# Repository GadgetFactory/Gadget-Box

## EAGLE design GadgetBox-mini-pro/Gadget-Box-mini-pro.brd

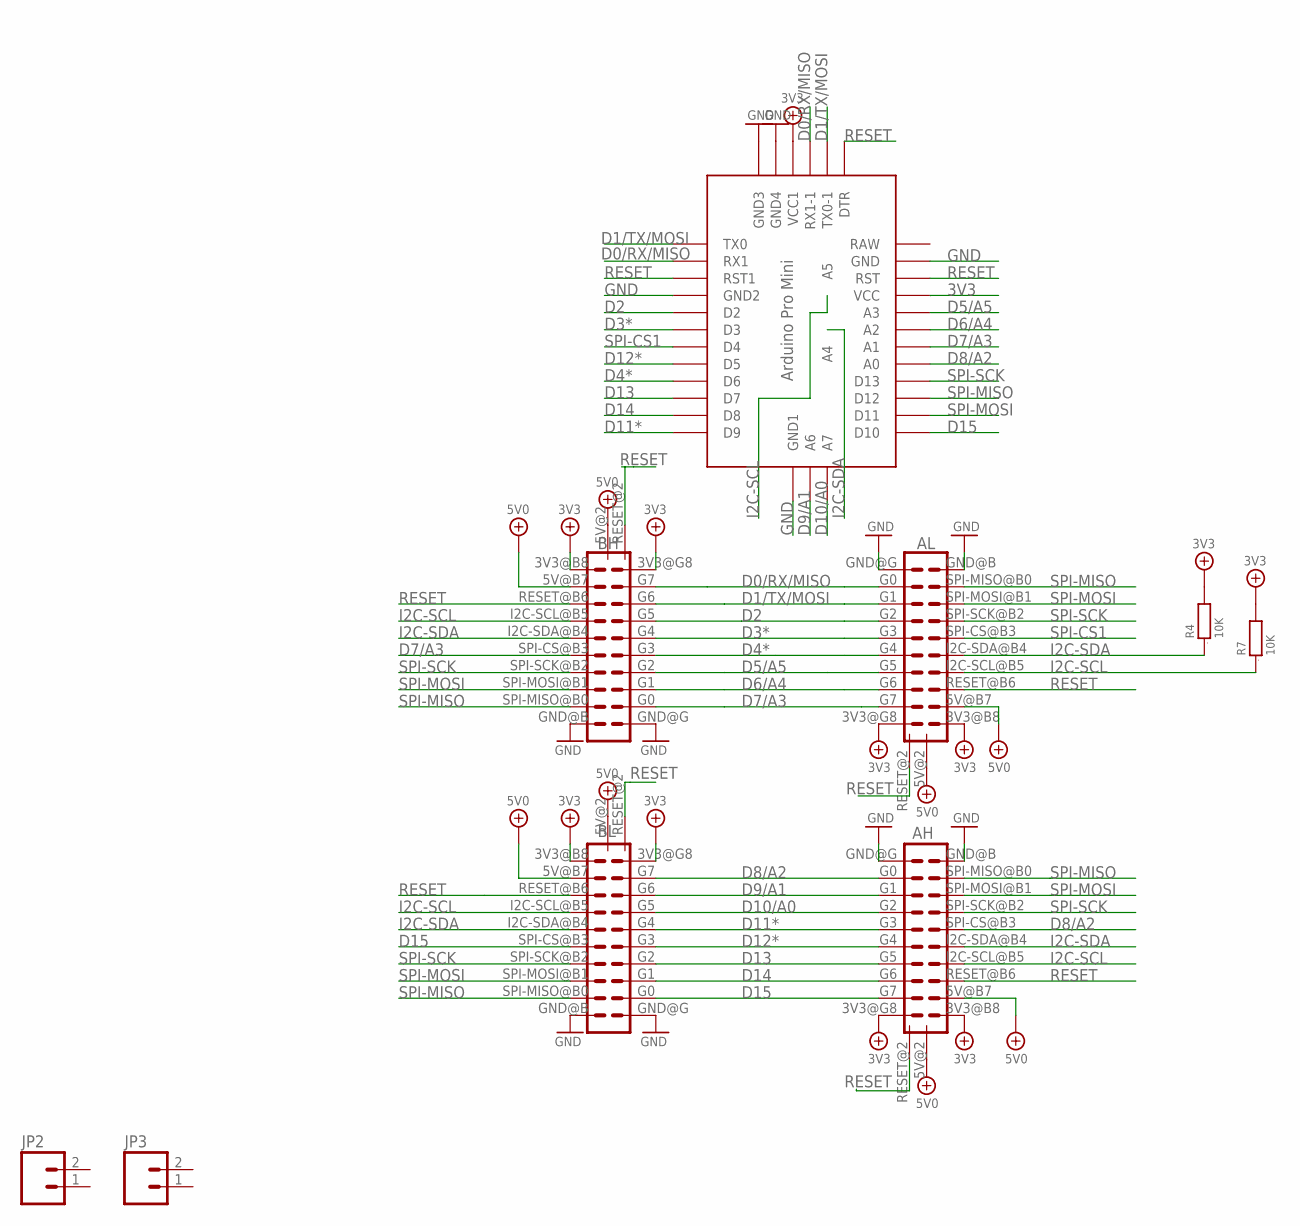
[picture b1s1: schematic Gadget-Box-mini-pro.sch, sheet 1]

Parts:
AH: ECOGECOG_SLOT_ALT1; ECOG_ALT1; PARTNO PPPC102LFBN-RC,SULLINS CONNECTOR SOLUTI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
AL: ECOGECOG_SLOT_ALT1; ECOG_ALT1; PARTNO PPPC102LFBN-RC,SULLINS CONNECTOR SOLUTI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
BH: ECOGECOG_SLOT_ALT1; ECOG_ALT1; PARTNO PPPC102LFBN-RC,SULLINS CONNECTOR SOLUTI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
BL: ECOGECOG_SLOT_ALT1; ECOG_ALT1; PARTNO PPPC102LFBN-RC,SULLINS CONNECTOR SOLUTI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
JP2, JP3: M021X02_NO_SILK; 1X02_NO_SILK; PARTNO PPPC021LFBN-RC,SULLINS CONNECTOR SOLUTI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
R4, R7: 10K; 0603; PARTNO RC0603JR-0710KL,YAGEO (VA),dk,311-10KGR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
U$1: ABK-PRO-MINI

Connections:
3V3: AH.3V3@B8 (3V3), AH.3V3@G8 (3V3), AL.3V3@B8 (3V3), AL.3V3@G8 (3V3), BH.3V3@B8 (3V3), BH.3V3@G8 (3V3), BL.3V3@B8 (3V3), BL.3V3@G8 (3V3), R4.2, R7.2, U$1.VCC, U$1.VCC1; also elsewhere on the board
5V0: AH.5V@2 (5V), AH.5V@B7 (5V), AL.5V@2 (5V), AL.5V@B7 (5V), BH.5V@2 (5V), BH.5V@B7 (5V), BL.5V@2 (5V), BL.5V@B7 (5V); also elsewhere on the board
D0/RX/MISO: AL.G0, BH.G7, U$1.RX1, U$1.RX1-1
D1/TX/MOSI: AL.G1, BH.G6, U$1.TX0, U$1.TX0-1
D2: AL.G2, BH.G5, U$1.D2
D3*: AL.G3, BH.G4, U$1.D3
D4*: AL.G4, BH.G3, U$1.D6
D5/A5: AL.G5, BH.G2, U$1.A3; also elsewhere on the board
D6/A4: AL.G6, BH.G1, U$1.A2
D7/A3: AL.G7, BH.G0, BH.SPI-CS@B3 (SPI-CS), U$1.A1
D8/A2: AH.G0, AH.SPI-CS@B3 (SPI-CS), BL.G7, U$1.A0
D9/A1: AH.G1, BL.G6, U$1.A6
D10/A0: AH.G2, BL.G5, U$1.A7
D11*: AH.G3, BL.G4, U$1.D9
D12*: AH.G4, BL.G3, U$1.D5
D13: AH.G5, BL.G2, U$1.D7
D14: AH.G6, BL.G1, U$1.D8
D15: AH.G7, BL.G0, BL.SPI-CS@B3 (SPI-CS), U$1.D10
GND: AH.GND@B (GND), AH.GND@G (GND), AL.GND@B (GND), AL.GND@G (GND), BH.GND@B (GND), BH.GND@G (GND), BL.GND@B (GND), BL.GND@G (GND), U$1.GND, U$1.GND1 (GND2), U$1.GND2 (GND3), U$1.GND3 (GND4), U$1.GND4 (GND1); also elsewhere on the board
I2C-SCL: AH.I2C-SCL@B5 (I2C-SCL), AL.I2C-SCL@B5 (I2C-SCL), BH.I2C-SCL@B5 (I2C-SCL), BL.I2C-SCL@B5 (I2C-SCL), R7.1, U$1.A5
I2C-SDA: AH.I2C-SDA@B4 (I2C-SDA), AL.I2C-SDA@B4 (I2C-SDA), BH.I2C-SDA@B4 (I2C-SDA), BL.I2C-SDA@B4 (I2C-SDA), R4.1, U$1.A4
RESET: AH.RESET@2 (RESET), AH.RESET@B6 (RESET), AL.RESET@2 (RESET), AL.RESET@B6 (RESET), BH.RESET@2 (RESET), BH.RESET@B6 (RESET), BL.RESET@2 (RESET), BL.RESET@B6 (RESET), U$1.DTR, U$1.RST, U$1.RST1
SPI-CS1: AL.SPI-CS@B3 (SPI-CS), U$1.D4
SPI-MISO: AH.SPI-MISO@B0 (SPI-MISO), AL.SPI-MISO@B0 (SPI-MISO), BH.SPI-MISO@B0 (SPI-MISO), BL.SPI-MISO@B0 (SPI-MISO), U$1.D12
SPI-MOSI: AH.SPI-MOSI@B1 (SPI-MOSI), AL.SPI-MOSI@B1 (SPI-MOSI), BH.SPI-MOSI@B1 (SPI-MOSI), BL.SPI-MOSI@B1 (SPI-MOSI), U$1.D11
SPI-SCK: AH.SPI-SCK@B2 (SPI-SCK), AL.SPI-SCK@B2 (SPI-SCK), BH.SPI-SCK@B2 (SPI-SCK), BL.SPI-SCK@B2 (SPI-SCK), U$1.D13

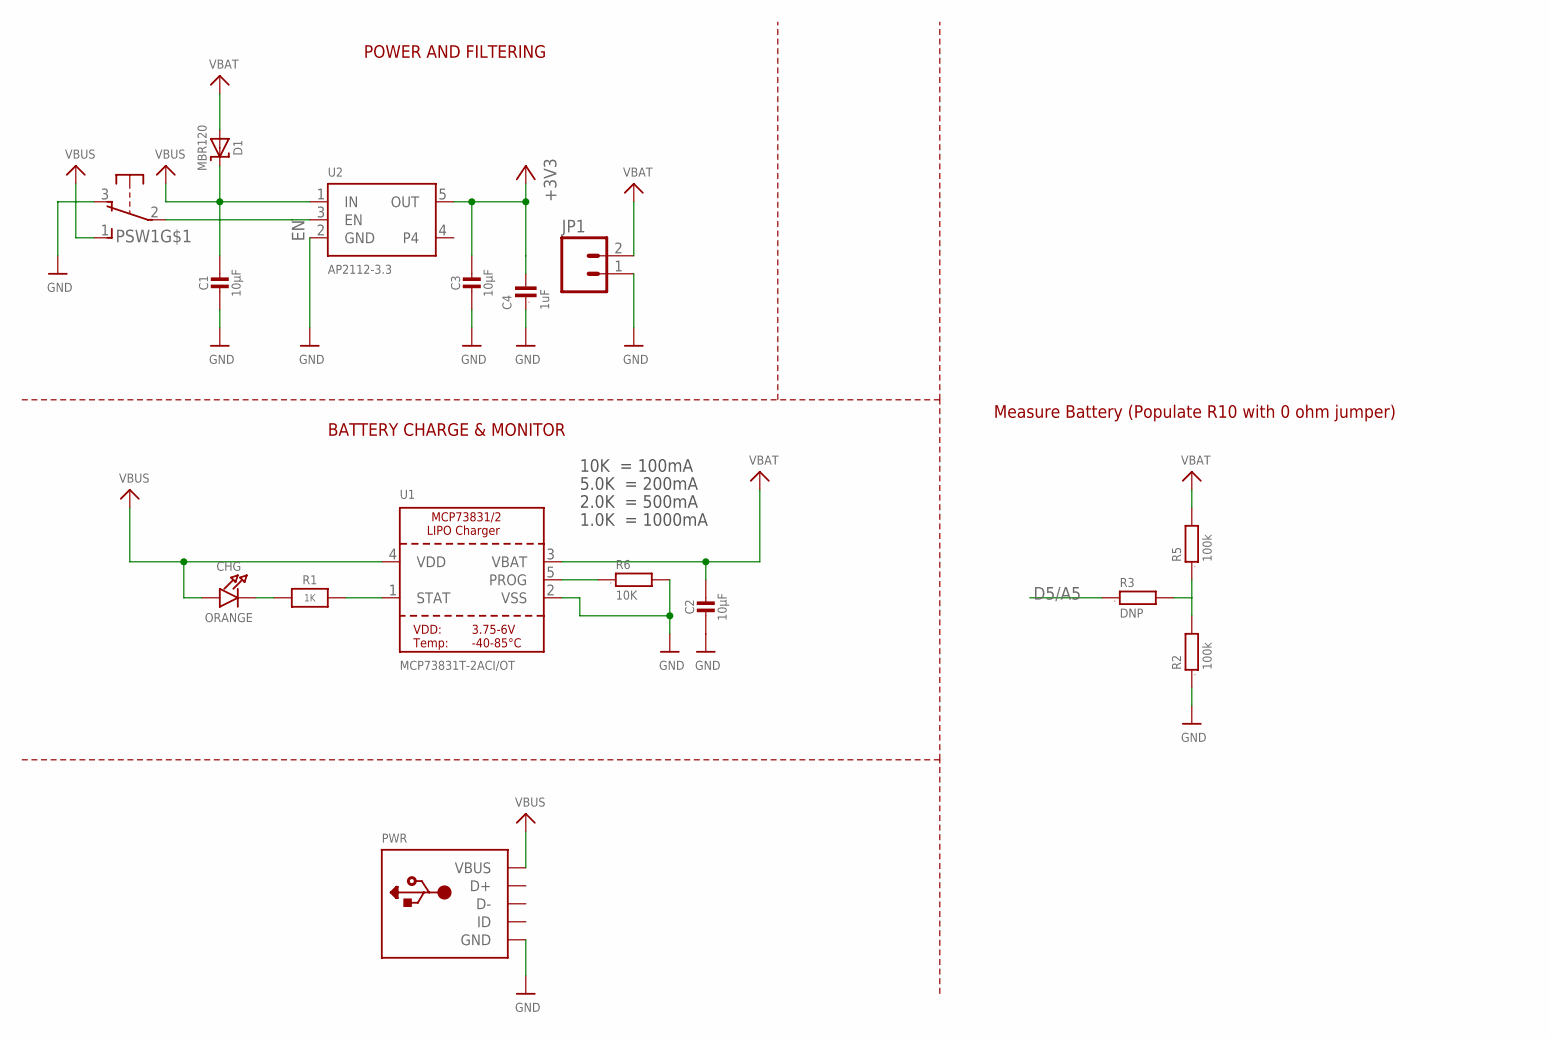
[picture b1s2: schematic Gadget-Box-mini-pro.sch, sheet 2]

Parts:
C1, C2, C3: 10µF; 0805-NO; PARTNO CL21F106ZPFNNNE,Samsung,DK,1276-3012-1-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
C4: 1uF; 0603; PARTNO C1608X5R1A105K080AC,TDK CORPORATION (VA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
CHG: ORANGE; CHIPLED_0805_NOOUTLINE; PARTNO LTST-C171EKT,LITE-ON INC (VA),DK,160-14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
D1: MBR120; SOD-123; PARTNO MBR120VLSFT3G,on semiconductor,dk,MBR12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
JP1: M02-JST-2-PTH-NO_SILK; JST-2-PTH-NS; PARTNO B2B-PH-SM4-TB(LF)(SN),JST SALES AMERICA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
PSW1: OS102011MA1Q; PARTNO OS102011MA1QN1,C&K Components,dk,CKN955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
PWR: USBMINIB; USB-MINIB; PARTNO USB-M26FTR,On Shore Technology Inc,DK,E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
R1: 1K; 0603-NO; PARTNO RC0603JR-071KL,YAGEO (VA),dk,311-1.0KGR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
R2, R5: 100k; 0603; PARTNO RC0603JR-07100KL,YAGEO (VA),dk,311-100K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
R3: DNP; 0603
R6: 10K; 0603; PARTNO RC0603JR-0710KL,YAGEO (VA),dk,311-10KGR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
U1: MCP73831T-2ACI/OT; SOT23-5; PARTNO MCP73831T-2ACI/OT,MICROCHIP TECHNOLOGY 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
U2: AP2112-3.3; SOT23-5; PARTNO AP2112K-3.3TRG1,Diodes Incorporated,dk,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

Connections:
3V3: C3.1, C4.2, U2.5 (OUT); also elsewhere on the board
5V0: C1.1, CHG.A, D1.C, PSW1.1 (S), PWR.VBUS, U1.4 (VDD), U2.1 (IN); also elsewhere on the board
D5/A5: R3.1; also elsewhere on the board
EN: PSW1.2, U2.3 (EN)
GND: C1.2, C2.2, C3.2, C4.1, JP1.1, PSW1.3 (O), PWR.GND, R2.1, R6.2, U1.2 (VSS), U2.2 (GND); also elsewhere on the board
unnamed: CHG.C, R1.1
unnamed: R2.2, R3.2, R5.1
unnamed: R1.2, U1.1 (STAT)
unnamed: R6.1, U1.5 (PROG)
VBAT: C2.1, D1.A, JP1.2, R5.2, U1.3 (VBAT)

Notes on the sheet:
POWER AND FILTERING
10K = 100mA
5.0K = 200mA
2.0K = 500mA
1.0K = 1000mA
BATTERY CHARGE & MONITOR
Measure Battery (Populate R10 with 0 ohm jumper)

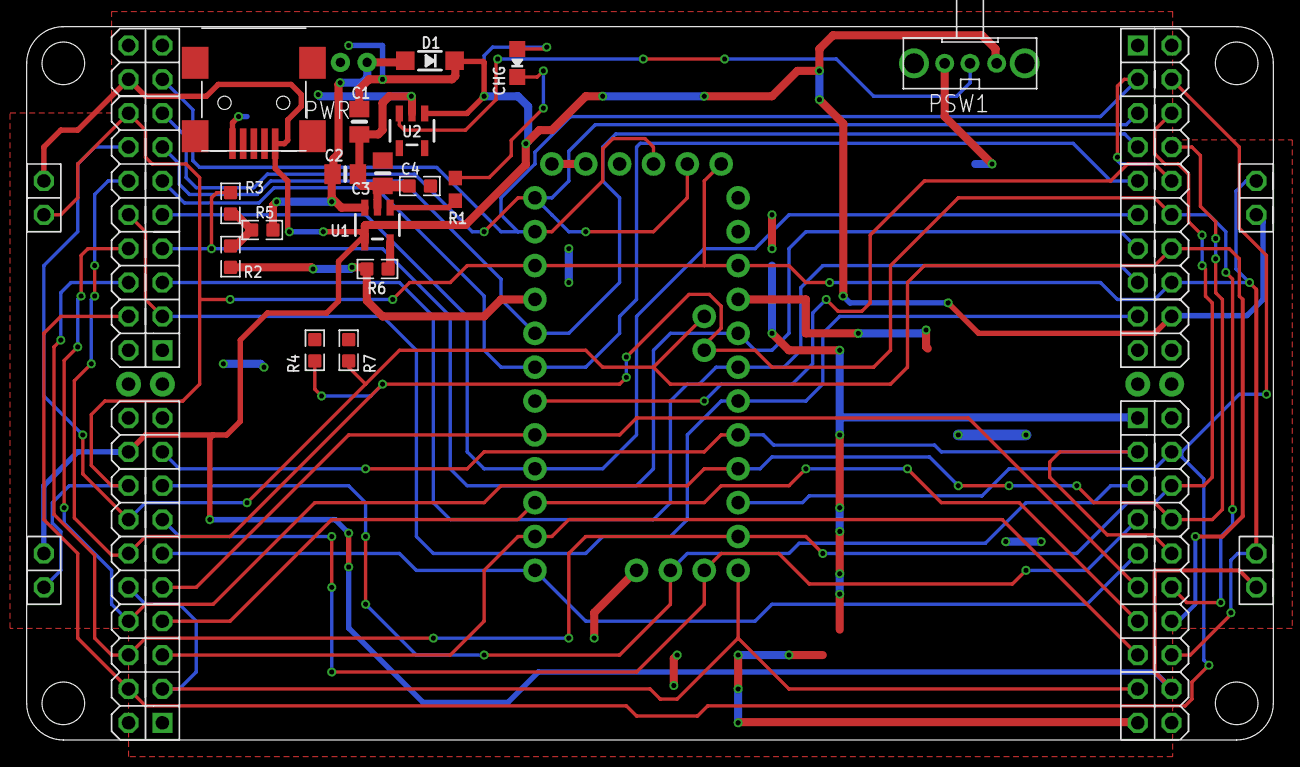
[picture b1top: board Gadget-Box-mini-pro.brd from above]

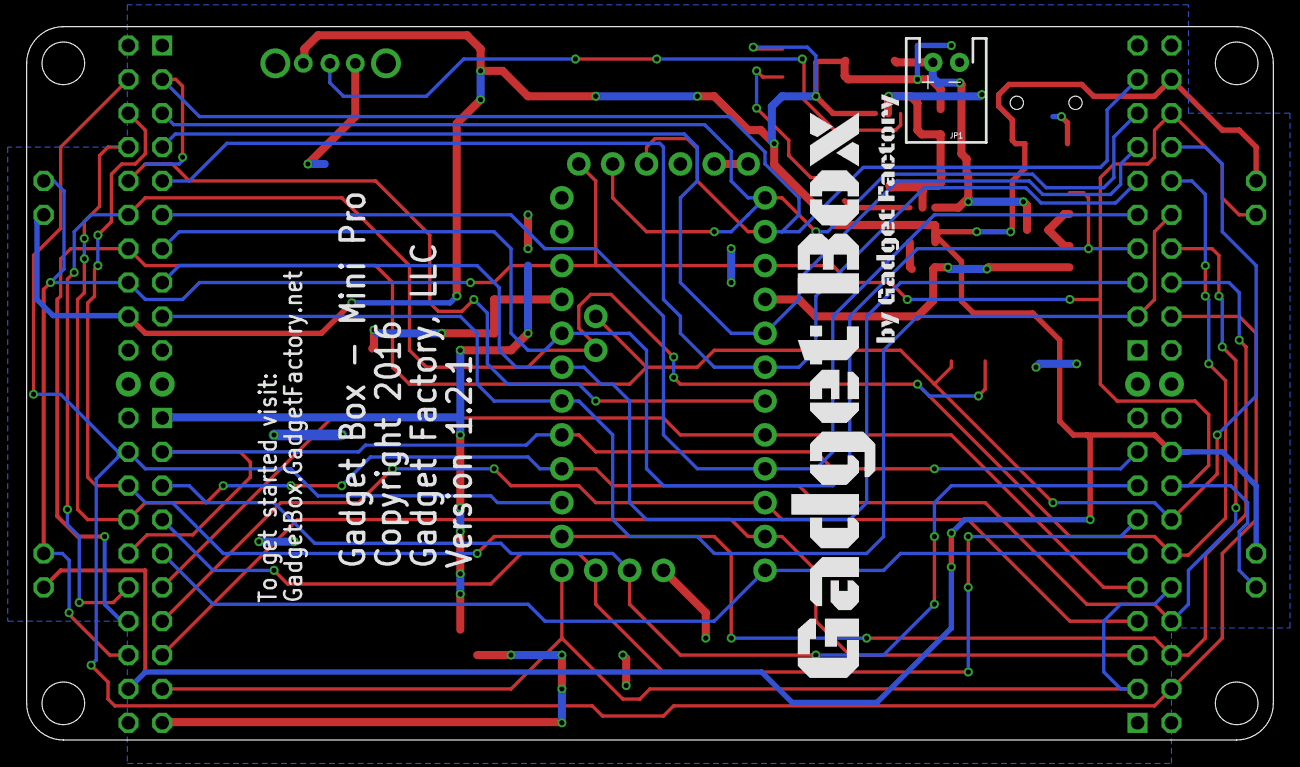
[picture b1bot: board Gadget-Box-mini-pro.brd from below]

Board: 2 copper layers, 93.5 x 53.5 mm, 27 parts (2 on the bottom side), 32 nets.

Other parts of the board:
$$U$1: ECOG93P53P5
U$100: GADGETBOX_TEXT

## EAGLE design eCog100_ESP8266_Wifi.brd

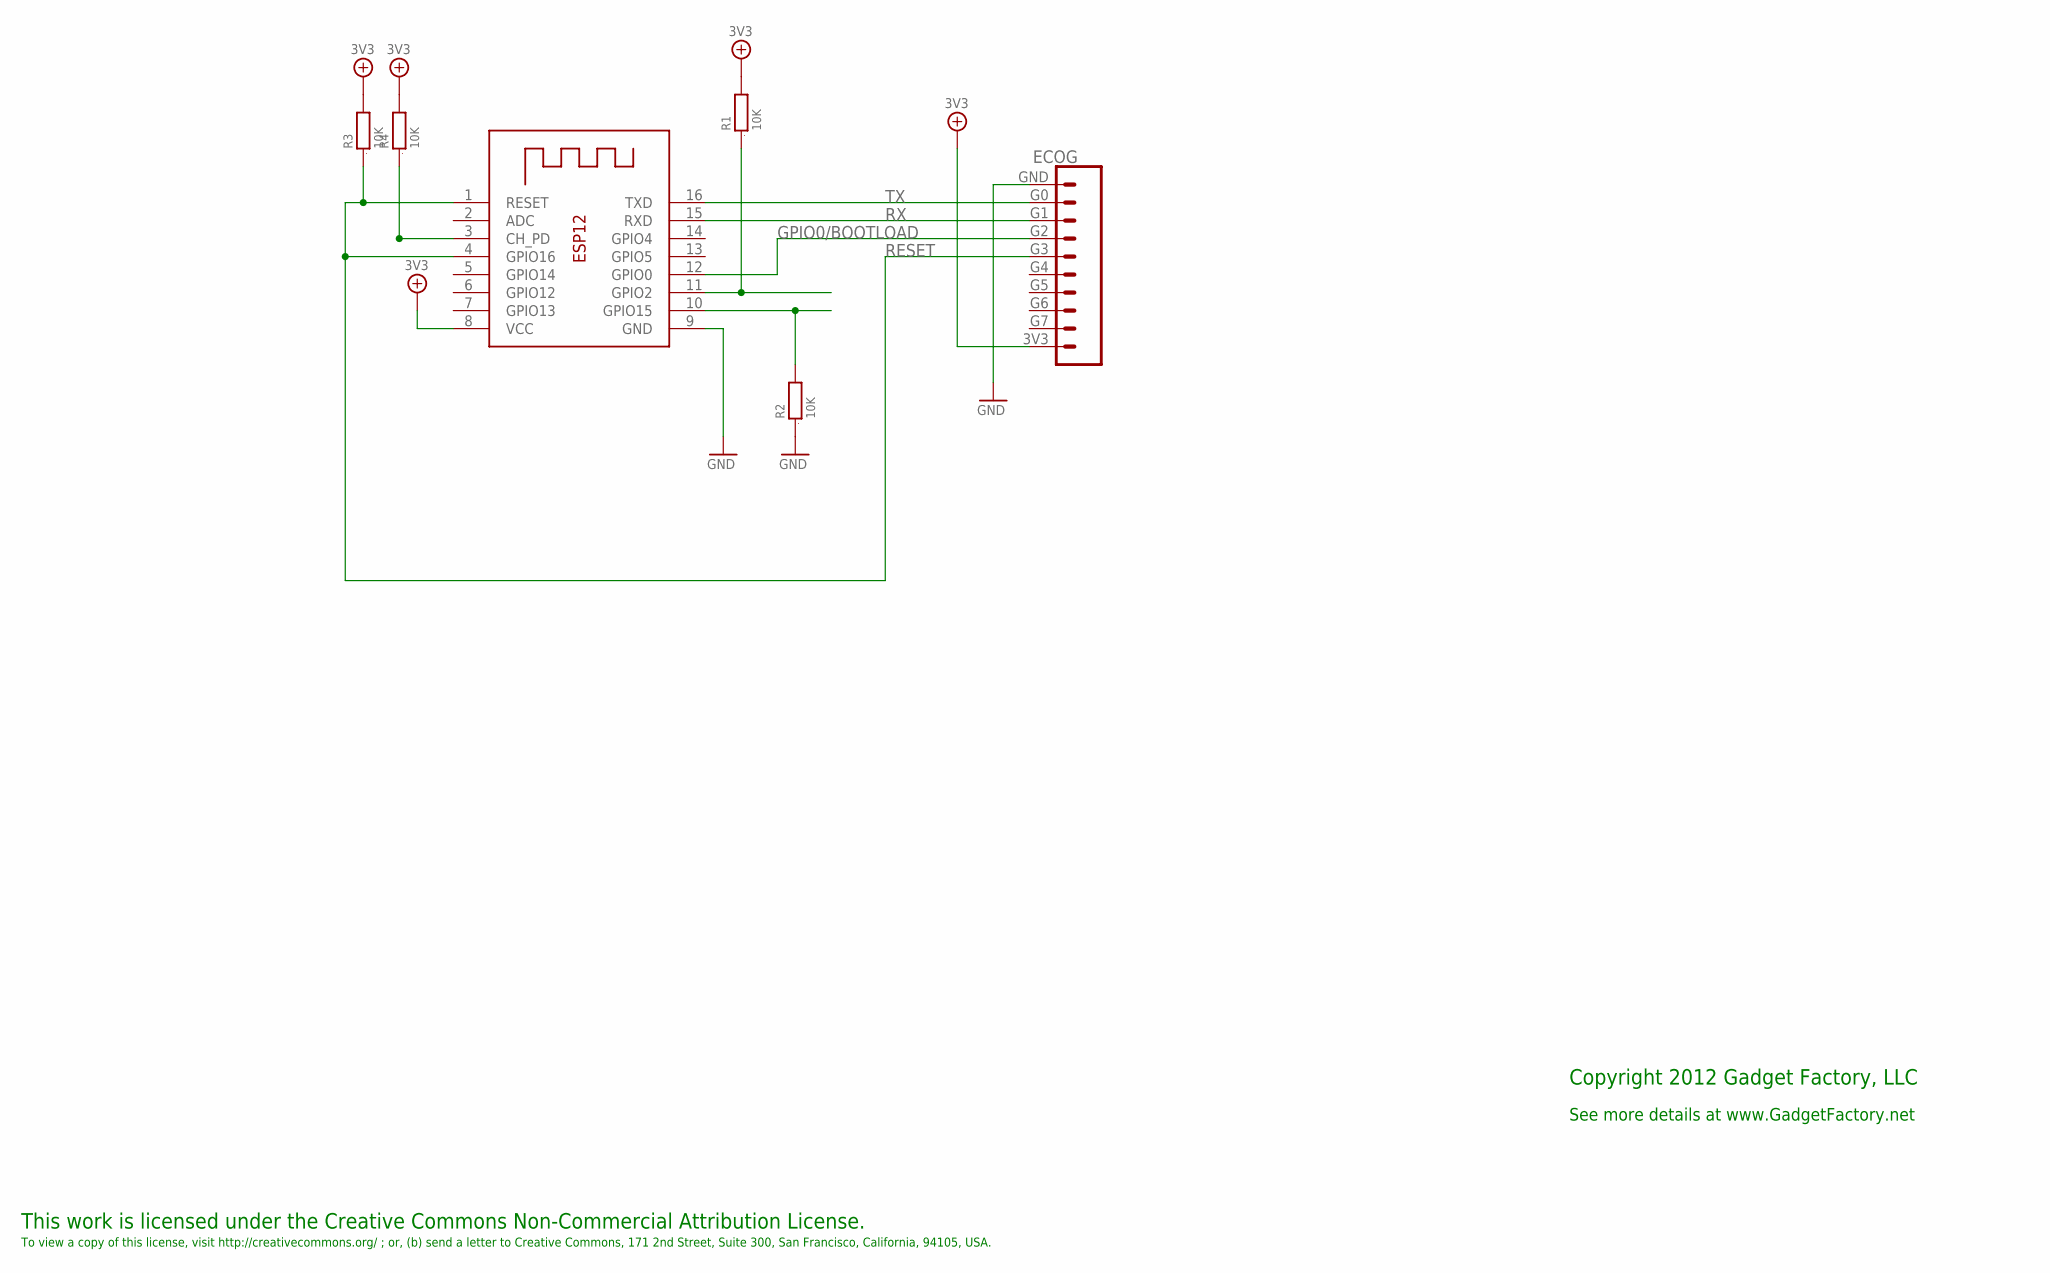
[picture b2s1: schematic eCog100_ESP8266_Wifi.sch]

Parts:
ECOG: ECOG_GENERAL_ROWECOG_GENERAL_SMD; ECOG_GENERAL_SMD
R1, R2, R3, R4: 10K; 0805; DIGIKEY RMCF0805JT10K0CT-ND
X1: ESP-12

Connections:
3V3: ECOG.3V3, R1.2, R3.2, R4.2, X1.8 (VCC)
GND: ECOG.GND, R2.1, X1.9 (GND)
GPIO0/BOOTLOAD: ECOG.G2, X1.12 (GPIO0)
unnamed: R1.1, X1.11 (GPIO2)
unnamed: R2.2, X1.10 (GPIO15)
unnamed: R4.1, X1.3 (CH_PD)
RESET: ECOG.G3, R3.1, X1.1 (RESET), X1.4 (GPIO16)
RX: ECOG.G1, X1.15 (RXD)
TX: ECOG.G0, X1.16 (TXD)

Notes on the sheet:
This work is licensed under the Creative Commons Non-Commercial Attribution License.
To view a copy of this license, visit http://creativecommons.org/ ; or, (b) send a letter to Creative Commons, 171 2nd Street, Suite 300, San Francisco, California, 94105, USA.
Copyright 2012 Gadget Factory, LLC
See more details at www.GadgetFactory.net

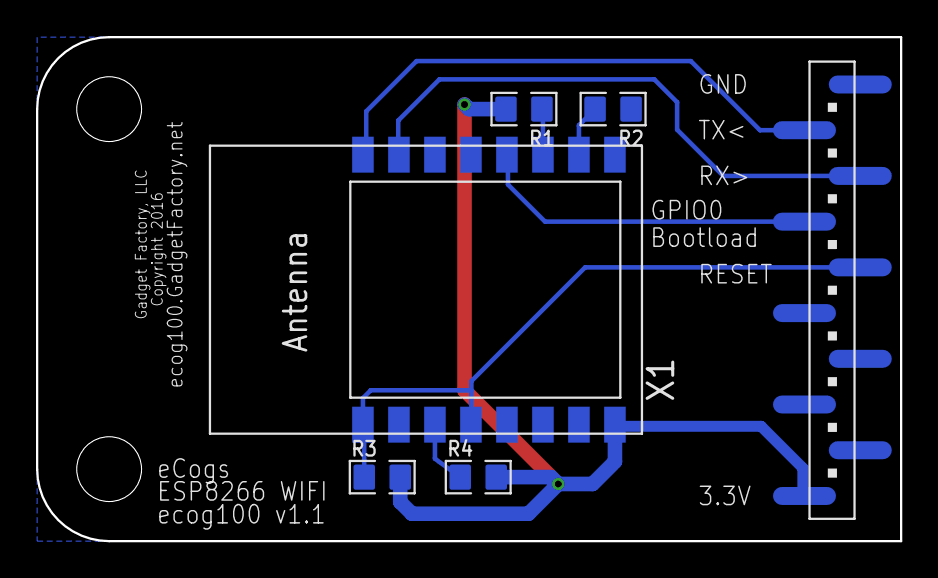
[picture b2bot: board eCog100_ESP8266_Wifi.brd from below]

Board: 2 copper layers, 48.0 x 28.0 mm, 12 parts (5 on the bottom side), 9 nets.

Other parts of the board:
U$1: GADGETBOX_TEXT
U$2, U$3, U$4, U$5: LEGEND_DIO
U$6: OSHW_FILLX200_NOTEXT

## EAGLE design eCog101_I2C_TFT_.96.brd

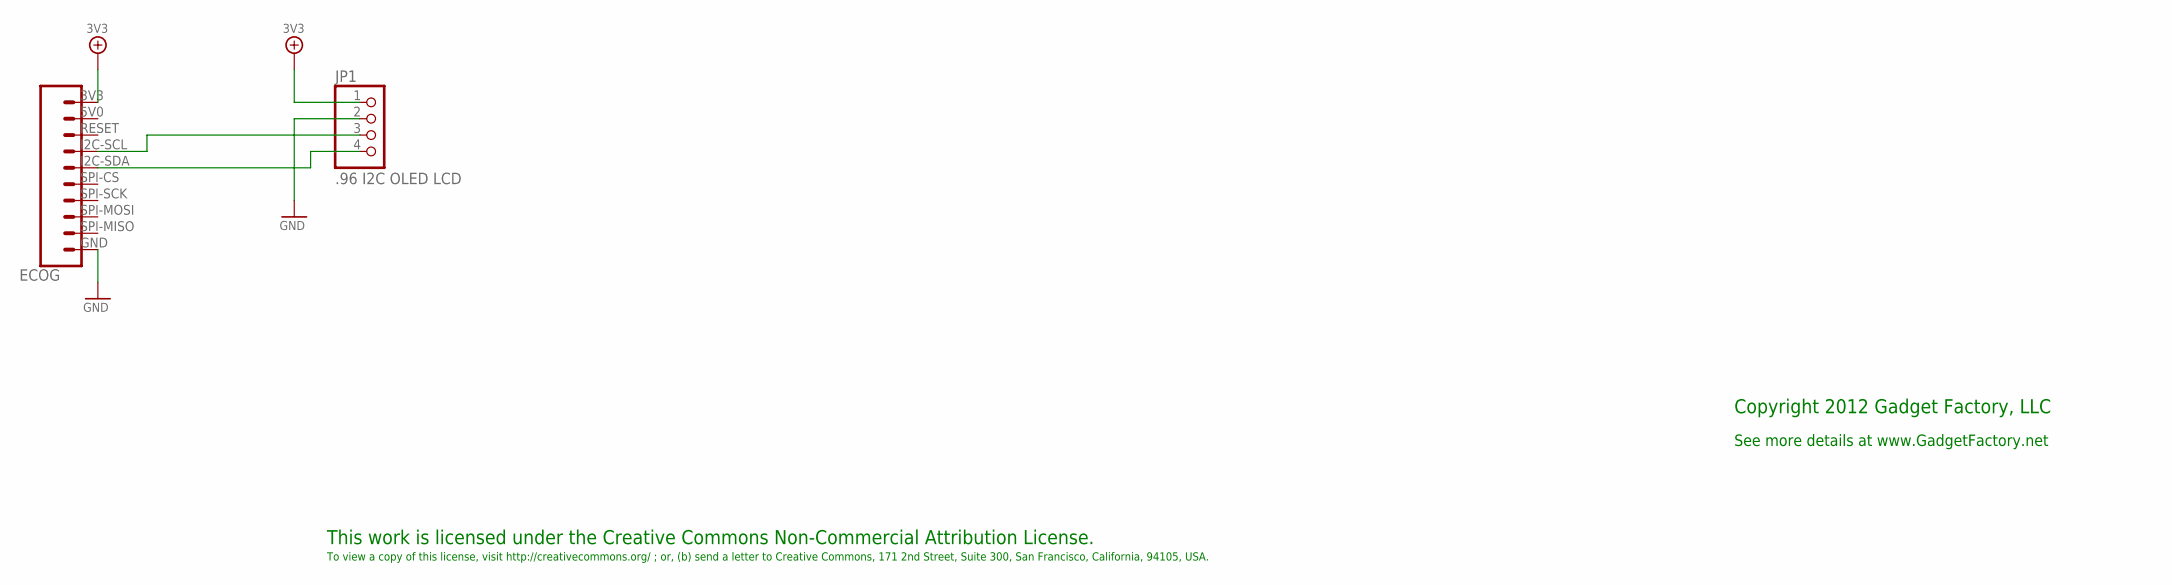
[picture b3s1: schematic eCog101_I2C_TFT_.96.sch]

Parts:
ECOG: ECOG_BUSES_ROWECOG_BUSES_SMD; ECOG_BUSES_SMD
JP1: .96 I2C OLED LCD; 1X04

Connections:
3V3: ECOG.3V3, JP1.1
GND: ECOG.GND, JP1.2
unnamed: ECOG.I2C-SCL, JP1.3
unnamed: ECOG.I2C-SDA, JP1.4

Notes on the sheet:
This work is licensed under the Creative Commons Non-Commercial Attribution License.
To view a copy of this license, visit http://creativecommons.org/ ; or, (b) send a letter to Creative Commons, 171 2nd Street, Suite 300, San Francisco, California, 94105, USA.
Copyright 2012 Gadget Factory, LLC
See more details at www.GadgetFactory.net

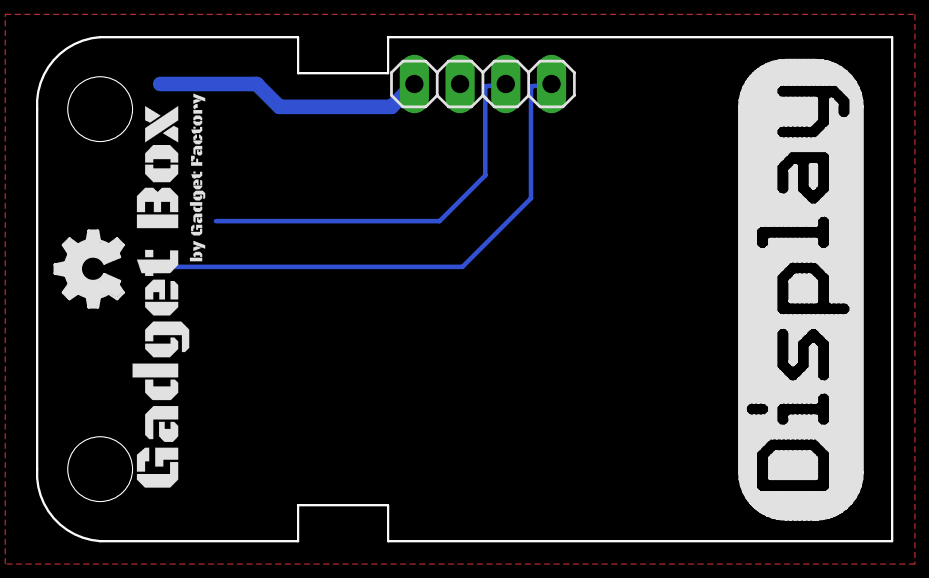
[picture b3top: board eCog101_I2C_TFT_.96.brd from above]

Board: 2 copper layers, 47.5 x 28.0 mm, 4 parts (0 on the bottom side), 4 nets.

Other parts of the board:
U$1: GADGETBOX_SMALL
U$2: OSHW_FILLX150_NOTEXT

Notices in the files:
GadgetBox-mini-pro/Gadget-Box-mini-pro.brd:
Copyright 2016
parts and their libraries:
microbuilder: This work is placed in the public domain, and may be freely used for commercial and non-commercial work with the following conditions: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
SparkFun: Licensing: CC v3.0 Share-Alike You are welcome to use this library for commercial purposes.
